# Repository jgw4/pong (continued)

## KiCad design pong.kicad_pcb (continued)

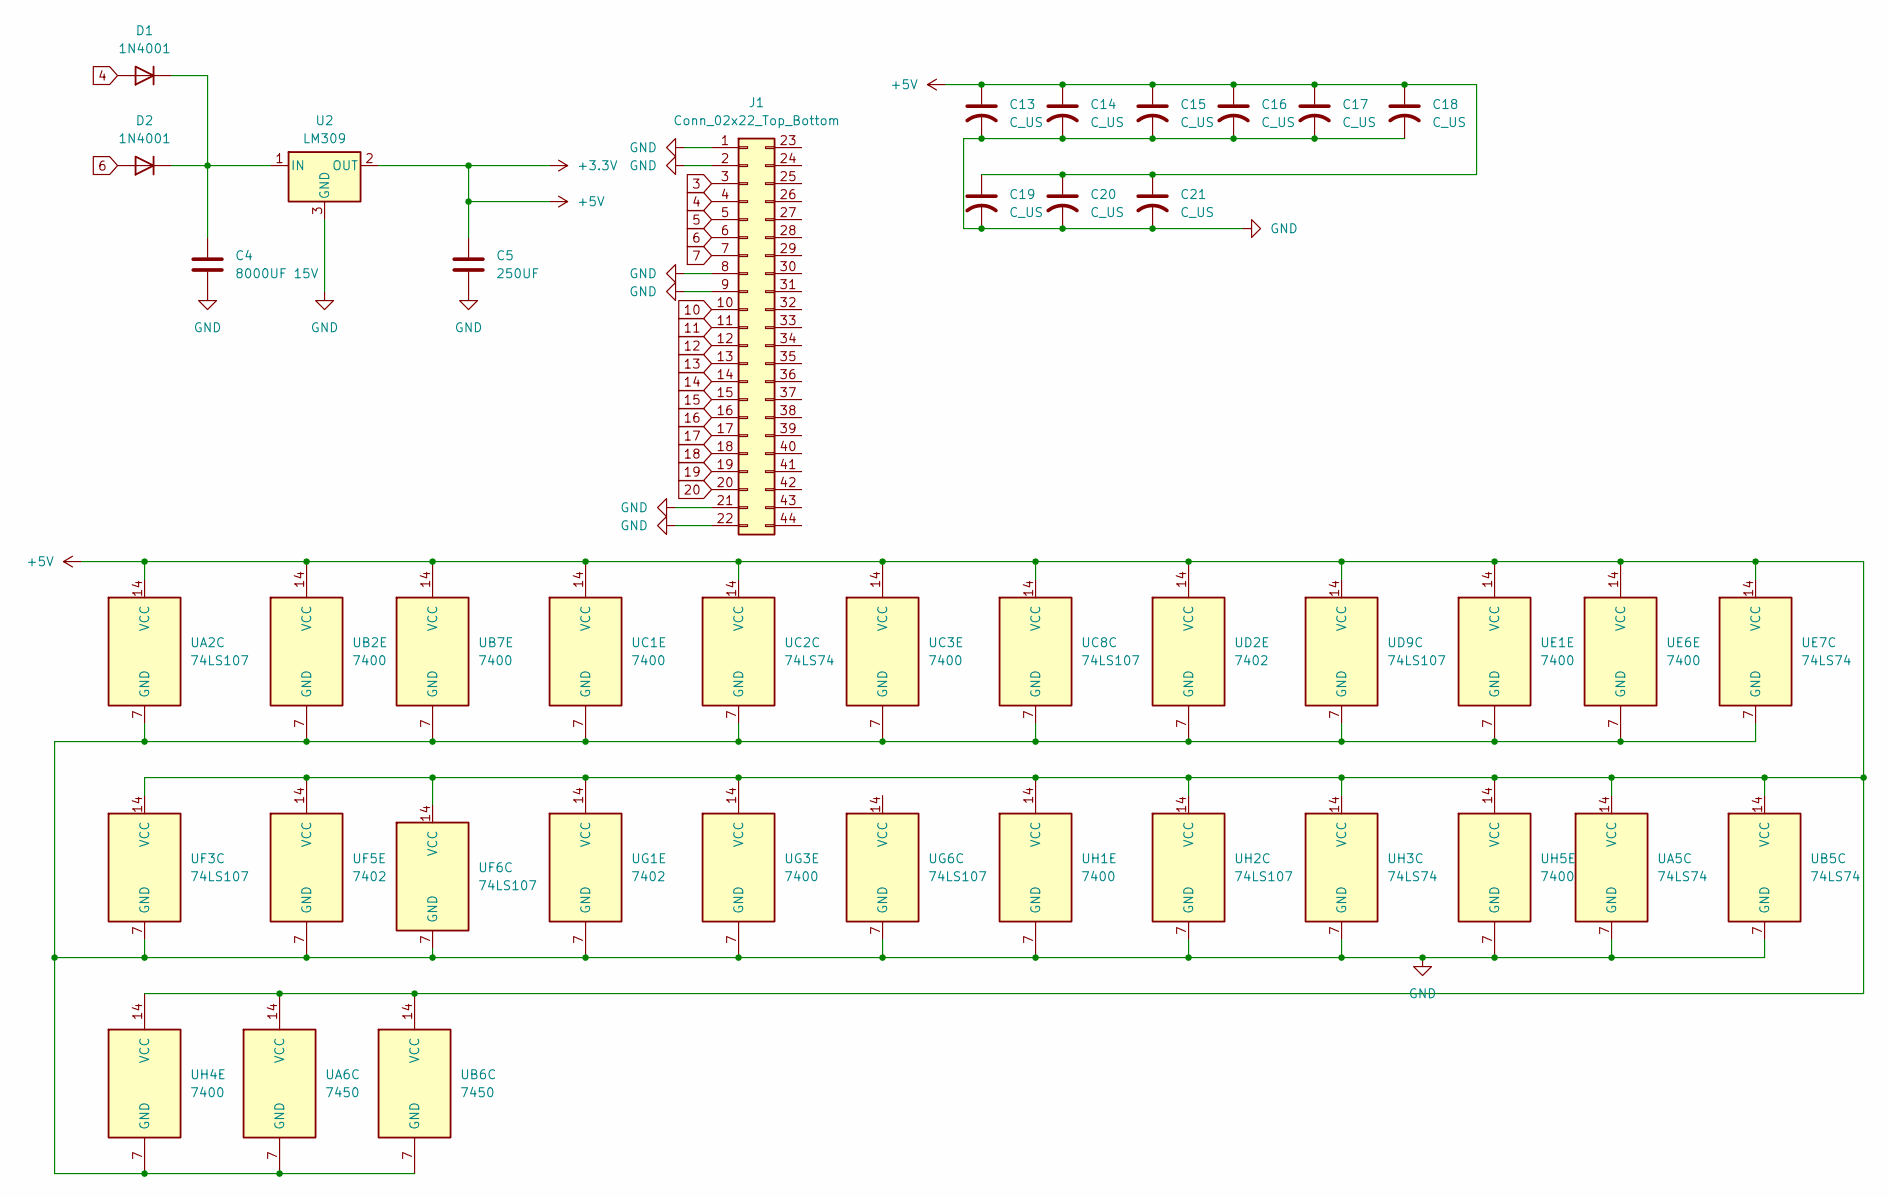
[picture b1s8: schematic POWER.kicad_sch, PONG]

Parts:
C4: 8000UF 15V
C5: 250UF
C13, C14, C15, C16, C17, C18, C19, C20, C21: C_US; C_Disc_D16.0mm_W5.0mm_P10.00mm
D1, D2: 1N4001; D_DO-41_SOD81_P10.16mm_Horizontal
J1: Conn_02x22_Top_Bottom
U2: LM309; TO-3
UA2: 74LS107; pong_DIP-14_W7.62mm_Socket_LongPads
UA5: 74LS74; pong_DIP-14_W7.62mm_Socket_LongPads
UA6: 7450; pong_DIP-14_W7.62mm_Socket_LongPads
UB2, UB7: 7400; pong_DIP-14_W7.62mm_Socket_LongPads
UB5: 74LS74; pong_DIP-14_W7.62mm_Socket_LongPads
UB6: 7450; pong_DIP-14_W7.62mm_Socket_LongPads
UC1, UC3: 7400; pong_DIP-14_W7.62mm_Socket_LongPads
UC2: 74LS74; pong_DIP-14_W7.62mm_Socket_LongPads
UC8: 74LS107; pong_DIP-14_W7.62mm_Socket_LongPads
UD2: 7402; pong_DIP-14_W7.62mm_Socket_LongPads
UD9: 74LS107; pong_DIP-14_W7.62mm_Socket_LongPads
UE1, UE6: 7400; pong_DIP-14_W7.62mm_Socket_LongPads
UE7: 74LS74; pong_DIP-14_W7.62mm_Socket_LongPads
UF3, UF6: 74LS107; pong_DIP-14_W7.62mm_Socket_LongPads
UF5: 7402; pong_DIP-14_W7.62mm_Socket_LongPads
UG1: 7402; pong_DIP-14_W7.62mm_Socket_LongPads
UG3: 7400; pong_DIP-14_W7.62mm_Socket_LongPads
UG6: 74LS107; pong_DIP-14_W7.62mm_Socket_LongPads
UH1, UH4, UH5: 7400; pong_DIP-14_W7.62mm_Socket_LongPads
UH2: 74LS107; pong_DIP-14_W7.62mm_Socket_LongPads
UH3: 74LS74; pong_DIP-14_W7.62mm_Socket_LongPads

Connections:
+3.3V: C5.1, C13.1, C14.1, C15.1, C16.1, C17.1, C18.1, C19.1, C20.1, C21.1, U2.2 (OUT), UA2.14 (VCC), UA5.14 (VCC), UA6.14 (VCC), UB2.14 (VCC), UB5.14 (VCC), UB6.14 (VCC), UB7.14 (VCC), UC1.14 (VCC), UC2.14 (VCC), UC3.14 (VCC), UC8.14 (VCC), UD2.14 (VCC), UD9.14 (VCC), UE1.14 (VCC), UE6.14 (VCC), UE7.14 (VCC), UF3.14 (VCC), UF5.14 (VCC), UF6.14 (VCC), UG1.14 (VCC), UG3.14 (VCC), UH1.14 (VCC), UH2.14 (VCC), UH3.14 (VCC), UH4.14 (VCC), UH5.14 (VCC); also elsewhere on the board
GND: C4.2, C5.2, C13.2, C14.2, C15.2, C16.2, C17.2, C18.2, C19.2, C20.2, C21.2, J1.1, J1.2, J1.8, J1.9, J1.21, J1.22, U2.3 (GND), UA2.7 (GND), UA5.7 (GND), UA6.7 (GND), UB2.7 (GND), UB5.7 (GND), UB6.7 (GND), UB7.7 (GND), UC1.7 (GND), UC2.7 (GND), UC3.7 (GND), UC8.7 (GND), UD2.7 (GND), UD9.7 (GND), UE1.7 (GND), UE6.7 (GND), UE7.7 (GND), UF3.7 (GND), UF5.7 (GND), UF6.7 (GND), UG1.7 (GND), UG3.7 (GND), UG6.7 (GND), UH1.7 (GND), UH2.7 (GND), UH3.7 (GND), UH4.7 (GND), UH5.7 (GND); also elsewhere on the board
unnamed: C4.1, D1.1 (K_1), D2.1 (K_1), U2.1 (IN)
unnamed: D1.2 (A), J1.4
unnamed: D2.2 (A), J1.6

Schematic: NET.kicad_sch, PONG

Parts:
R18: R; R_Axial_DIN0207_L6.3mm_D2.5mm_P10.16mm_Horizontal
UF3: 74LS107; pong_DIP-14_W7.62mm_Socket_LongPads
UG2: 7427; pong_DIP-14_W7.62mm_Socket_LongPads
UG3: 7400; pong_DIP-14_W7.62mm_Socket_LongPads

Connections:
4V: UG2.3; also elsewhere on the board
256H: UF3.8 (J), UG3.4; also elsewhere on the board
+3.3V: R18.2, UG2.14 (VCC); also elsewhere on the board
CLOCK: UF3.9 (C)
GND: UG2.7 (GND); also elsewhere on the board
NET: UG2.6; also elsewhere on the board
unnamed: UF3.6 (~Q), UG3.5
unnamed: R18.1, UF3.10 (~R)
unnamed: UG2.5, UG3.6
VBLANK: UG2.4; also elsewhere on the board
/256H: UF3.11 (K); also elsewhere on the board

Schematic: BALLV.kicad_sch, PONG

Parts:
UA3: 74LS161; pong_DIP-16_W7.62mm_Socket_LongPads
UB2: 7400; pong_DIP-14_W7.62mm_Socket_LongPads
UB3: 74LS161; pong_DIP-16_W7.62mm_Socket_LongPads
UD2: 7402; pong_DIP-14_W7.62mm_Socket_LongPads
UE2: 7410; pong_DIP-14_W7.62mm_Socket_LongPads

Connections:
+3.3V: UA3.16 (VCC), UB3.16 (VCC), UE2.14 (VCC); also elsewhere on the board
A6: UB3.3 (D0); also elsewhere on the board
B6: UB3.4 (D1); also elsewhere on the board
C6: UB3.5 (D2); also elsewhere on the board
D6: UB3.6 (D3); also elsewhere on the board
GND: UA3.3 (D0), UA3.4 (D1), UA3.5 (D2), UA3.6 (D3), UA3.8 (GND), UB3.8 (GND), UE2.7 (GND); also elsewhere on the board
unnamed: UA3.7 (CEP), UB2.5, UB3.15 (TC)
unnamed: UA3.1 (~MR), UA3.10 (CET), UB3.1 (~MR), UB3.7 (CEP)
unnamed: UA3.15 (TC), UB2.4, UE2.5
unnamed: UA3.9 (~PE), UB2.6, UB3.9 (~PE)
unnamed: UB3.12 (Q2), UE2.3
unnamed: UB3.11 (Q3), UE2.4
VVID: UD2.13; also elsewhere on the board
/HSYNC: UA3.2 (CP), UB3.2 (CP); also elsewhere on the board
/VBLANK: UB3.10 (CET); also elsewhere on the board
/VVID: UD2.11, UD2.12, UE2.6; also elsewhere on the board

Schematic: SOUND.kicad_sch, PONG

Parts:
C6: 1.0; C_Axial_L3.8mm_D2.6mm_P10.00mm_Horizontal
C7: .1; C_Axial_L3.8mm_D2.6mm_P10.00mm_Horizontal
R6: R; R_Axial_DIN0207_L6.3mm_D2.5mm_P10.16mm_Horizontal
R7: 220K; R_Axial_DIN0207_L6.3mm_D2.5mm_P10.16mm_Horizontal
UC1, UC3: 7400; pong_DIP-14_W7.62mm_Socket_LongPads
UC2: 74LS74; pong_DIP-14_W7.62mm_Socket_LongPads
UF3: 74LS107; pong_DIP-14_W7.62mm_Socket_LongPads
UG4: NE555P; DIP-8_W7.62mm_Socket_LongPads

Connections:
32V: UC3.9; also elsewhere on the board
+3.3V: R6.1, R7.1, UG4.4 (~RST), UG4.8 (VCC); also elsewhere on the board
GND: C6.2, C7.2, UG4.1 (GND); also elsewhere on the board
HIT SOUND EN: UC2.6 (~Q), UC3.1, UC3.3
unnamed: R6.2, UC2.2 (D), UC2.4 (~S)
unnamed: UC3.5, UF3.3 (Q)
unnamed: C7.1, UG4.5 (CONT)
unnamed: C6.1, R7.2, UG4.6 (THRES), UG4.7 (DISCH)
unnamed: UC3.10, UG4.3 (OUT)
SCORESOUND: UC3.8
VBLANK: UF3.12 (C); also elsewhere on the board
VPOS16: UC3.2
VPOS32: UC3.4
VPOS256: UC2.3 (C)
VVID: UF3.1 (J); also elsewhere on the board
/ATTRACT: UC1.4; also elsewhere on the board
/HIT: UC2.1 (~R)
/MISS: UG4.2 (TRIG); also elsewhere on the board
/SERVE: UF3.13 (~R)
/VVID: UF3.4 (K); also elsewhere on the board

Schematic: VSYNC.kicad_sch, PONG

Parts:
R16, R17: R; R_Axial_DIN0207_L6.3mm_D2.5mm_P10.16mm_Horizontal
UD8: 7410; pong_DIP-14_W7.62mm_Socket_LongPads
UD9: 74LS107; pong_DIP-14_W7.62mm_Socket_LongPads
UE7: 74LS74; pong_DIP-14_W7.62mm_Socket_LongPads
UE8, UE9: 7493; pong_DIP-14_W7.62mm_Socket_LongPads

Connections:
+3.3V: R16.1, R17.1, UD8.14 (VCC), UE8.5 (VCC), UE9.5 (VCC); also elsewhere on the board
/VSYNC/1V: UD8.11, UE8.1 (~CKB), UE8.12 (Q0)
/VSYNC/2V: UE8.9 (Q1)
/VSYNC/4V: UD8.10, UE8.8 (Q2)
/VSYNC/8V: UE8.11 (Q3), UE9.14 (~CKA)
/VSYNC/16V: UE9.1 (~CKB), UE9.12 (Q0)
/VSYNC/32V: UE9.9 (Q1)
/VSYNC/64V: UE9.8 (Q2)
/VSYNC/128V: UD9.9 (C), UE9.11 (Q3)
/VSYNC/V RESET: UE7.6 (~Q), UE8.2 (R0(1)), UE8.3 (R0(2)), UE9.2 (R0(1)), UE9.3 (R0(2))
/VSYNC//V RESET: UD9.10 (~R), UE7.5 (Q)
CLK: UE7.3 (C); also elsewhere on the board
GND: UD8.7 (GND), UE8.10 (GND), UE9.10 (GND); also elsewhere on the board
HRESET: UE8.14 (~CKA); also elsewhere on the board
unnamed: R16.2, UD9.8 (J), UD9.11 (K)
unnamed: UD8.9, UD9.5 (Q)
unnamed: UD8.8, UE7.2 (D)
unnamed: R17.2, UE7.1 (~R), UE7.4 (~S)
/256V: UD9.6 (~Q); also elsewhere on the board

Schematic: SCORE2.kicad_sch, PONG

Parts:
R24: R; R_Axial_DIN0207_L6.3mm_D2.5mm_P10.16mm_Horizontal
UC3: 7400; pong_DIP-14_W7.62mm_Socket_LongPads
UC4: 7410; pong_DIP-14_W7.62mm_Socket_LongPads
UD2: 7402; pong_DIP-14_W7.62mm_Socket_LongPads
UD3: 7430; pong_DIP-14_W7.62mm_Socket_LongPads
UD4, UD5: 7410; pong_DIP-14_W7.62mm_Socket_LongPads
UE2: 7410; pong_DIP-14_W7.62mm_Socket_LongPads
UE4: 7404; pong_DIP-14_W7.62mm_Socket_LongPads
UE5: 7427; pong_DIP-14_W7.62mm_Socket_LongPads

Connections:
4H: UC3.12, UE5.10; also elsewhere on the board
4V: UE2.1, UE5.4; also elsewhere on the board
8H: UC3.13, UE5.11
8V: UE2.2, UE5.3; also elsewhere on the board
16H: UE2.13, UE4.3; also elsewhere on the board
16V: UD5.4, UD5.10, UD5.13, UE4.5; also elsewhere on the board
+3.3V: R24.1, UC4.14 (VCC), UD3.14 (VCC), UD4.14 (VCC), UD5.14 (VCC), UE2.14 (VCC), UE4.14 (VCC), UE5.14 (VCC); also elsewhere on the board
/SCORE2/scoreA: UD4.11, UE5.6
/SCORE2/scoreBC: UC4.9, UD2.4, UD5.1
/SCORE2/scoreFE: UD4.13, UD5.11, UE5.8
/SCORE2/scoreGD: UD4.4, UD5.3, UE4.2
GND: UC4.7 (GND), UD3.7 (GND), UD4.7 (GND), UD5.7 (GND), UE2.7 (GND), UE4.7 (GND), UE5.7 (GND); also elsewhere on the board
unnamed: R24.2, UD3.1
unnamed: UC3.11, UD2.5
unnamed: UC4.8, UD3.4
unnamed: UC4.10, UD4.1, UD4.5, UD4.10, UE4.6
unnamed: UD2.6, UE4.4, UE5.5, UE5.9
unnamed: UD3.2, UD5.12
unnamed: UD3.3, UD5.6
unnamed: UD3.5, UD5.8
unnamed: UD3.6, UD4.6
unnamed: UD3.11, UD4.8
unnamed: UD3.12, UD4.12
unnamed: UE2.12, UE4.1
SCORE: UD3.8; also elsewhere on the board
a: UD4.9; also elsewhere on the board
b: UC4.11; also elsewhere on the board
c: UD5.2; also elsewhere on the board
d: UD5.5; also elsewhere on the board
e: UD5.9; also elsewhere on the board
f: UD4.2; also elsewhere on the board
g: UD4.3; also elsewhere on the board

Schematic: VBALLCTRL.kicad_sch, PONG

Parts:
R25: R; R_Axial_DIN0207_L6.3mm_D2.5mm_P10.16mm_Horizontal
UA4: 7486; pong_DIP-14_W7.62mm_Socket_LongPads
UA5: 74LS74; pong_DIP-14_W7.62mm_Socket_LongPads
UA6: 7450; pong_DIP-14_W7.62mm_Socket_LongPads
UB2: 7400; pong_DIP-14_W7.62mm_Socket_LongPads
UB4: 7483; pong_DIP-16_W7.62mm_Socket_LongPads
UB5: 74LS74; pong_DIP-14_W7.62mm_Socket_LongPads
UB6: 7450; pong_DIP-14_W7.62mm_Socket_LongPads
UC4: 7410; pong_DIP-14_W7.62mm_Socket_LongPads
UD1: 7404; pong_DIP-14_W7.62mm_Socket_LongPads

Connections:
256H: UA6.5, UA6.9, UB6.5; also elsewhere on the board
+3.3V: R25.1, UA4.14 (VCC), UB4.5 (VCC), UC4.14 (VCC), UD1.14 (VCC); also elsewhere on the board
A6: UB4.9 (S1); also elsewhere on the board
ATTRACT: UD1.5; also elsewhere on the board
B1: UA6.10
B2: UA6.1
B6: UB4.6 (S2); also elsewhere on the board
C1: UA6.3
C2: UA6.4
C6: UB4.2 (S3); also elsewhere on the board
D1: UB6.3
D2: UB6.4
D6: UB4.15 (S4); also elsewhere on the board
GND: UA4.7 (GND), UB4.1 (A4), UB4.12 (GND), UB4.13 (C0), UB4.16 (B4), UC4.7 (GND), UD1.7 (GND); also elsewhere on the board
HIT: UA5.3 (C), UA5.11 (C), UB2.12, UB2.13, UB5.3 (C); also elsewhere on the board
unnamed: UA4.4, UA4.10, UB6.1
unnamed: UA5.2 (D), UA6.6
unnamed: UA4.5, UA5.5 (Q)
unnamed: UA5.1 (~R), UA5.13 (~R), UB5.1 (~R), UD1.6
unnamed: UA5.4 (~S), UA5.10 (~S), UB5.4 (~S)
unnamed: UA5.12 (D), UA6.8
unnamed: UA4.9, UA5.9 (Q)
unnamed: UA4.8, UB4.10 (A1)
unnamed: UA4.6, UB4.8 (A2)
unnamed: UB4.3 (A3), UB6.8, UC4.1, UC4.2, UC4.13
unnamed: UB4.11 (B1), UC4.12
unnamed: R25.2, UB4.4 (B3), UB4.7 (B2)
unnamed: UB5.2 (D), UB6.6
unnamed: UB5.5 (Q), UB6.13
unnamed: UB5.6 (~Q), UB6.10
/256H: UA6.2, UA6.13, UB6.2; also elsewhere on the board

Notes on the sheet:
NEED H2A?

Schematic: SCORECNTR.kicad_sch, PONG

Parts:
R28, R29: R; R_Axial_DIN0207_L6.3mm_D2.5mm_P10.16mm_Horizontal
SW1: SW_DPDT_x2
UC7: 7490; pong_DIP-14_W7.62mm_Socket_LongPads
UC8: 74LS107; pong_DIP-14_W7.62mm_Socket_LongPads
UD1: 7404; pong_DIP-14_W7.62mm_Socket_LongPads
UD7: 7490; pong_DIP-14_W7.62mm_Socket_LongPads
UD8: 7410; pong_DIP-14_W7.62mm_Socket_LongPads
UE1, UE6: 7400; pong_DIP-14_W7.62mm_Socket_LongPads
UF5: 7402; pong_DIP-14_W7.62mm_Socket_LongPads
UH6: 7420; pong_DIP-14_W7.62mm_Socket_LongPads

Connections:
+3.3V: R28.1, R29.1, UC7.5 (VCC), UD1.14 (VCC), UD7.5 (VCC), UD8.14 (VCC), UH6.14 (VCC); also elsewhere on the board
/SCORECNTR/HVID: UE6.9, UH6.6
/SCORECNTR//MISS: UD1.13, UE6.8
GND: UC7.6 (R9(1)), UC7.7 (R9(2)), UC7.10 (GND), UD1.7 (GND), UD7.6 (R9(1)), UD7.7 (R9(2)), UD7.10 (GND), UD8.7 (GND), UH6.7 (GND); also elsewhere on the board
HBLANK: UE6.10
L: UF5.5
MISSED: UE1.3, UF5.2, UF5.6
unnamed: SW1.2 (B), UD8.2
unnamed: SW1.5 (B), UD8.4
unnamed: UC7.14 (~CKA), UF5.4
unnamed: R28.2, UC8.1 (J), UC8.4 (K)
unnamed: R29.2, UC8.8 (J), UC8.11 (K)
unnamed: UD1.12, UE1.1
unnamed: UD7.2 (R0(1)), UD7.3 (R0(2))
unnamed: UD7.14 (~CKA), UF5.1
R: UF5.3
SCORE1_1: UC7.1 (~CKB), UC7.12 (Q0), UD8.1; also elsewhere on the board
SCORE1_2: UC7.9 (Q1); also elsewhere on the board
SCORE1_4: SW1.3 (C), UC7.8 (Q2); also elsewhere on the board
SCORE1_8: UC7.11 (Q3), UC8.12 (C); also elsewhere on the board
SCORE1_10: UC8.3 (Q), UD8.13
SCORE2_1: UD7.1 (~CKB), UD7.12 (Q0), UD8.3; also elsewhere on the board
SCORE2_2: UD7.9 (Q1); also elsewhere on the board
SCORE2_4: SW1.6 (C), UD7.8 (Q2); also elsewhere on the board
SCORE2_8: UC8.9 (C), UD7.11 (Q3); also elsewhere on the board
SCORE2_10: UC8.5 (Q), UD8.5
SRST: UC7.2 (R0(1)), UC7.3 (R0(2))
/ATTRACT: UE1.2; also elsewhere on the board
/SCORE1_10: UC8.2 (~Q); also elsewhere on the board
/SRST: UC8.10 (~R), UC8.13 (~R); also elsewhere on the board
/STOPG1: UD8.12; also elsewhere on the board

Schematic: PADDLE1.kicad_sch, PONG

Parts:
C8: .1uF; C_Axial_L3.8mm_D2.6mm_P12.50mm_Horizontal
C9: .1uF; C_Axial_L3.8mm_D2.6mm_P10.00mm_Horizontal
D7: 1N914; D_DO-35_SOD27_P10.16mm_Horizontal
R10: 56K; R_Axial_DIN0207_L6.3mm_D2.5mm_P10.16mm_Horizontal
R11: R; R_Axial_DIN0207_L6.3mm_D2.5mm_P10.16mm_Horizontal
RV3: 50K
UA7: 7420; pong_DIP-14_W7.62mm_Socket_LongPads
UB7: 7400; pong_DIP-14_W7.62mm_Socket_LongPads
UB8: 7493; pong_DIP-14_W7.62mm_Socket_LongPads
UB9: NE555P; DIP-8_W7.62mm_Socket_LongPads
UC9: 7404; pong_DIP-14_W7.62mm_Socket_LongPads

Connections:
+3.3V: RV3.1, UA7.14 (VCC), UB8.5 (VCC), UB9.4 (~RST), UB9.8 (VCC), UC9.14 (VCC); also elsewhere on the board
/PADDLE1/B1: UA7.9, UB8.9 (Q1)
/PADDLE1/C1: UA7.12, UB8.8 (Q2)
/PADDLE1/D1: UA7.13, UB8.11 (Q3)
GND: C8.1, C9.1, UA7.7 (GND), UB8.10 (GND), UB9.1 (GND), UC9.7 (GND); also elsewhere on the board
unnamed: C9.2, R11.1
unnamed: C8.2, D7.2 (A), R10.2, UB9.6 (THRES)
unnamed: D7.1 (K), UB9.7 (DISCH)
unnamed: R10.1, RV3.2, RV3.3
unnamed: UA7.8, UB7.2, UB7.4
unnamed: UB7.1, UC9.4
unnamed: UA7.10, UB8.1 (~CKB), UB8.12 (Q0)
unnamed: UB8.2 (R0(1)), UB8.3 (R0(2)), UB9.3 (OUT), UC9.3
unnamed: UB7.6, UB8.14 (~CKA)
unnamed: R11.2, UB9.5 (CONT)
/256V: UB9.2 (TRIG); also elsewhere on the board
/HSYNC: UB7.5; also elsewhere on the board
/VPAD1: UB7.3; also elsewhere on the board

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
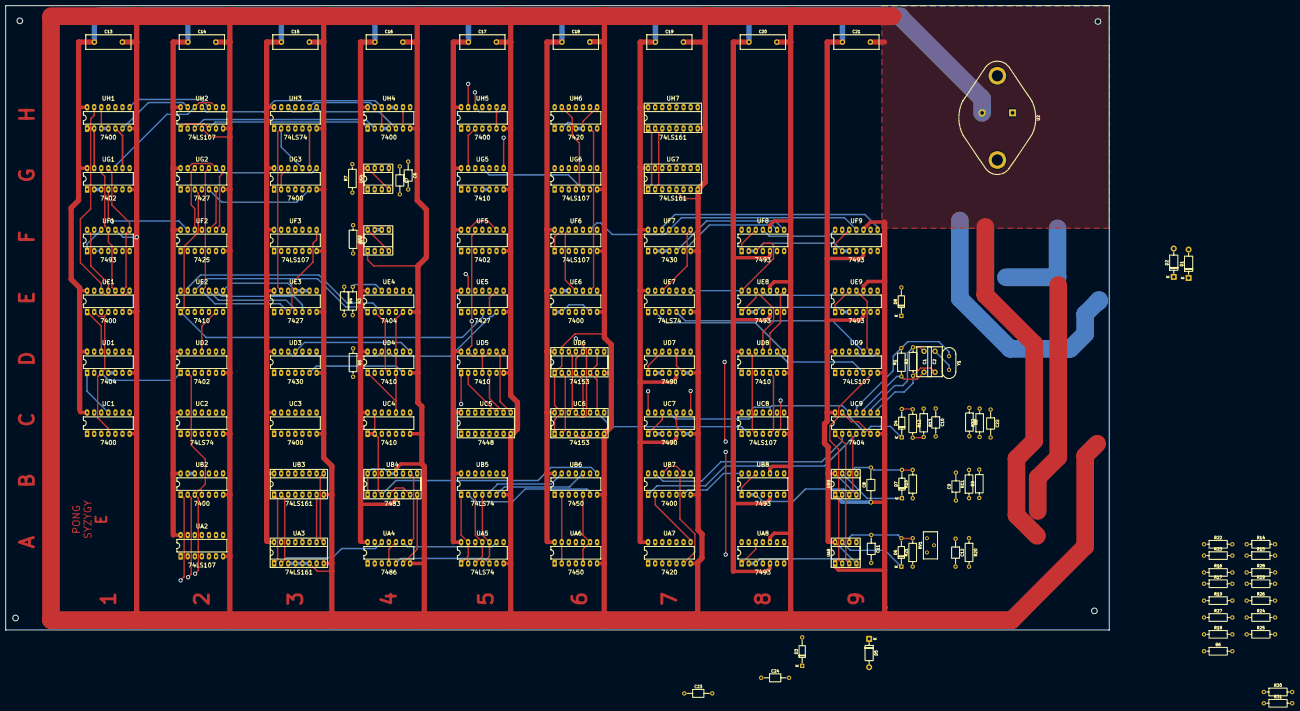
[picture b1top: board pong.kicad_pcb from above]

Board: 2 copper layers, 395.7 x 223.9 mm, 131 parts (0 on the bottom side), 245 nets.
